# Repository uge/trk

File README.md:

# nrf9151 based picoballoon tracker in kicad

This repo contains a KiCad 8.0 project which hopes to implement a low power tracker for pico-balloons
based on the nRF9151 module and a WSPR protocol modulator.

## Why the nRF9151?

The nRF9151 is marketed with emphasis on cellular data and GPS capabilities with optimization for power.
Trackers are one category of intended applications and the device and software stack have provisions for 
aggressive power saving modes. Even if the cellular data connectivity feature is not used, the nrf9151
is a power efficient microcontroller with an embedded GPS.

The cellular functionality opens up the possibility of eventually using NTN services such as Skylo or Starlink.

## WSPR modulator

The Si5351 is a common frequency synthesizer used to implement the WSPR protocol. This design opts
for the TI CDCE6214 in hopes of reducing power consumption and to try something different.

## Power conversion

Following the Traquito's example, this design uses buck-boost converters to adapt to varying and lower voltages.
This design uses the TI TPS631010 which can operate at input voltages from 1.6V to 5.5V. There are two
buck-boost converters for the 1.8V and 3.3V supplies respectively.

## Manufacturing

This design is targeted at JLCPCB 4 layer design rules and includes JLCPCB part numbers in the BOM.

## License and Copyright

Copyright 2024 - Eugene Feinberg (ugeook at gmail dot com)

Licensed under Creative Commons Attribution-NonCommercial 4.0 International Public License

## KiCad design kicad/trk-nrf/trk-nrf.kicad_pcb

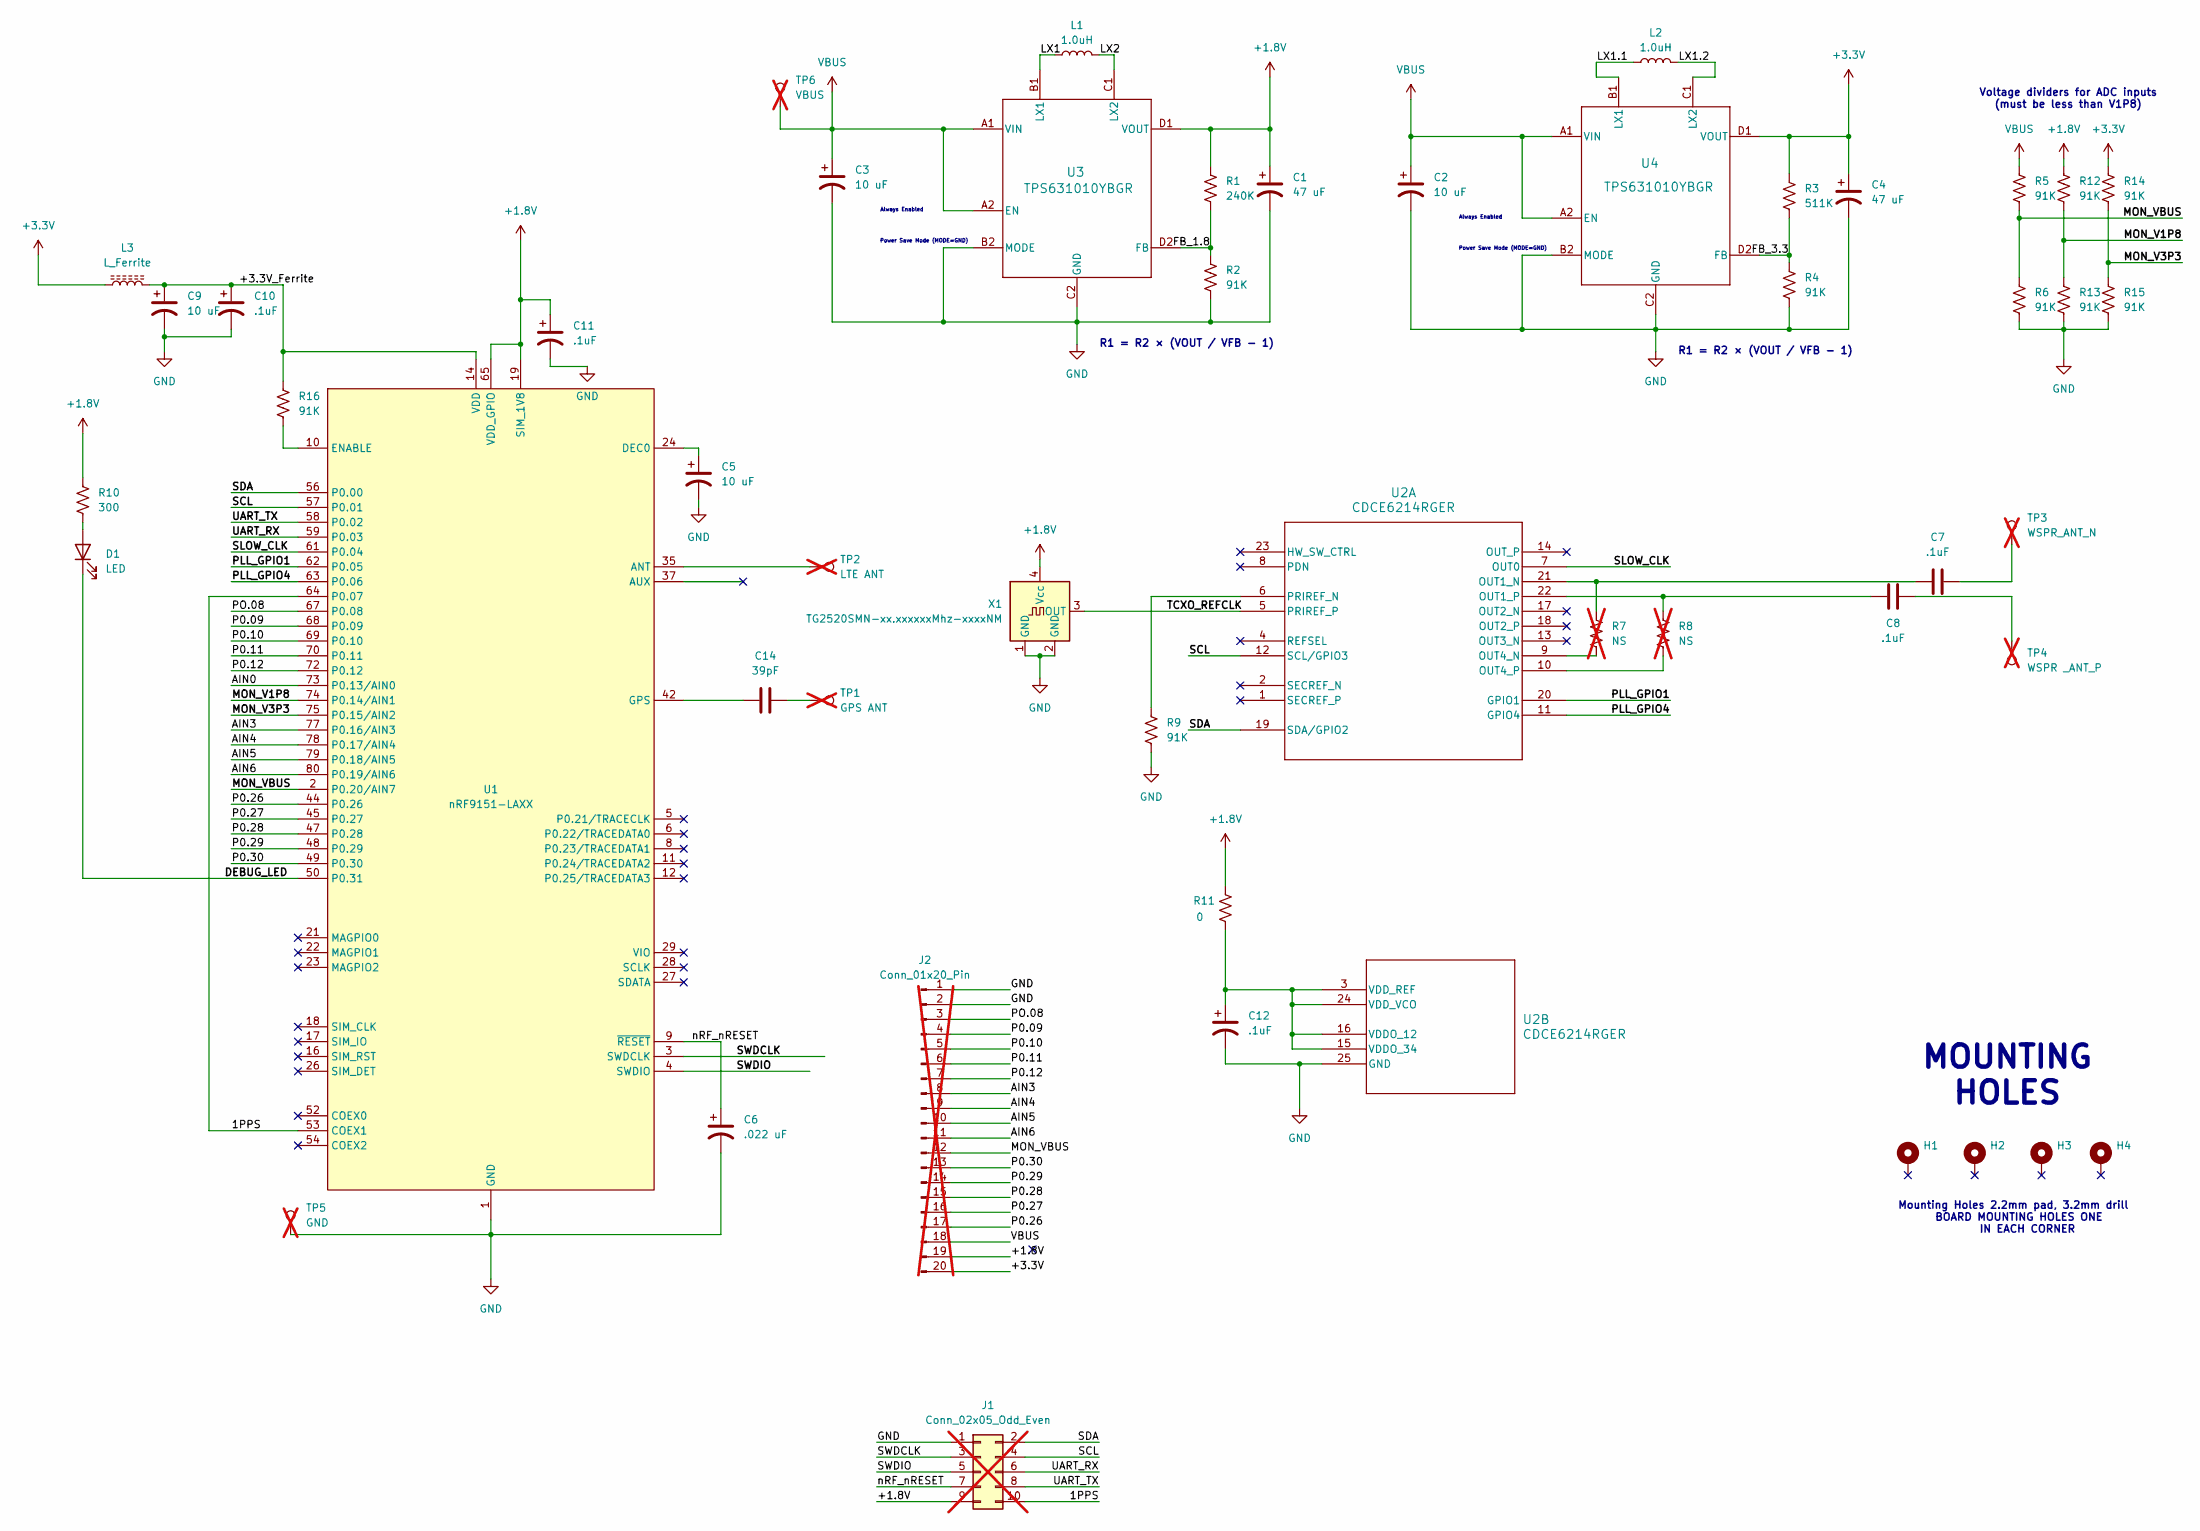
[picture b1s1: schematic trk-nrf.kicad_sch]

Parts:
C1, C4: 47 uF; C_0805_2012Metric; JLCPCB Part Number C16780
C2, C3, C5, C9: 10 uF; C_0603_1608Metric; JLCPCB Part Number C1691
C6: .022 uF; C_0402_1005Metric; JLCPCB Part Number C60474
C7, C8, C10, C11, C12: .1uF; C_0402_1005Metric; JLCPCB Part Number C1525
C14: 39pF; C_0402_1005Metric; JLCPCB Part Number C342946
D1: LED; LED_0402_1005Metric; JLCPCB Part Number C3007519
H1, H2, H3, H4: MountingHole_Pad_MP; MountingHole_2.2mm_M2_ISO7380_Pad
J1: Conn_02x05_Odd_Even; PinHeader_2x05_P1.00mm_Vertical_SMD; not fitted
J2: Conn_01x20_Pin; Hirose_FH12-20S-0.5SH_1x20-1MP_P0.50mm_Horizontal; not fitted
L1, L2: 1.0uH; L_Murata_DFE201610P; JLCPCB Part Number C92921
L3: L_Ferrite; L_0805_2012Metric; JLCPCB Part Number C12389
R1: 240K; R_0402_1005Metric; JLCPCB Part Number C64043
R2, R4, R5, R6, R9, R12, R13, R14, R15, R16: 91K; R_0402_1005Metric; JLCPCB Part Number C25573
R3: 511K; R_0402_1005Metric; JLCPCB Part Number C64042
R7, R8: NS; R_0402_1005Metric; not fitted
R10: 300; R_0402_1005Metric; JLCPCB Part Number C25159
R11: 0; R_0402_1005Metric; JLCPCB Part Number C17168
TP1: GPS ANT; TestPoint_Pad_1.5x1.5mm; not fitted
TP2: LTE ANT; TestPoint_Pad_1.5x1.5mm; not fitted
TP3: WSPR_ANT_N; TestPoint_THTPad_D1.5mm_Drill0.7mm; not fitted
TP4: WSPR _ANT_P; TestPoint_THTPad_D1.5mm_Drill0.7mm; not fitted
TP5: GND; TestPoint_THTPad_D1.5mm_Drill0.7mm; not fitted
TP6: VBUS; TestPoint_THTPad_D1.5mm_Drill0.7mm; not fitted
U1: nRF9151-LAXX; LGA_9151_12.1x11.1mm; JLCPCB Part Number C22397843
U2: CDCE6214RGER; VQFN24_RGE_TEX; JLCPCB Part Number C3608351
U3, U4: TPS631010YBGR; YBG0008; JLCPCB Part Number C6719123
X1: TG2520SMN-xx.xxxxxxMhz-xxxxNM; Oscillator_SMD_SeikoEpson_TG2520SMN-xxx-xxxxxx-4Pin_2.5x2.0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; JLCPCB Part Number C5590921

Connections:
+1.8V: C1.1, C11.1, J1.9, J2.19, R1.1, R10.1, R11.1, R12.1, U1.19 (SIM_1V8), U1.65 (VDD_GPIO), U3.D1 (VOUT), X1.4 (Vcc)
+3.3V: C4.1, J2.20, L3.1, R3.1, R14.1, U4.D1 (VOUT)
/1PPS: J1.10, U1.53 (COEX1), U1.64 (P0.07)
/+3.3V_Ferrite: C9.1, C10.1, L3.2, R16.1, U1.14 (VDD)
/AIN0: U1.73 (P0.13/AIN0)
/AIN3: J2.8, U1.77 (P0.16/AIN3)
/AIN4: J2.9, U1.78 (P0.17/AIN4)
/AIN5: J2.10, U1.79 (P0.18/AIN5)
/AIN6: J2.11, U1.80 (P0.19/AIN6)
/DEBUG_LED: D1.1 (K), U1.50 (P0.31)
/FB_1.8: R1.2, R2.1, U3.D2 (FB)
/FB_3.3: R3.2, R4.1, U4.D2 (FB)
/LX1: L1.1, U3.B1 (LX1)
/LX1.1: L2.1, U4.B1 (LX1)
/LX1.2: L2.2, U4.C1 (LX2)
/LX2: L1.2, U3.C1 (LX2)
/MON_V1P8: R12.2, R13.1, U1.74 (P0.14/AIN1)
/MON_V3P3: R14.2, R15.1, U1.75 (P0.15/AIN2)
/MON_VBUS: J2.12, R5.2, R6.1, U1.2 (P0.20/AIN7)
/P0.09: J2.4, U1.68 (P0.09)
/P0.10: J2.5, U1.69 (P0.10)
/P0.11: J2.6, U1.70 (P0.11)
/P0.12: J2.7, U1.72 (P0.12)
/P0.26: J2.17, U1.44 (P0.26)
/P0.27: J2.16, U1.45 (P0.27)
/P0.28: J2.15, U1.47 (P0.28)
/P0.29: J2.14, U1.48 (P0.29)
/P0.30: J2.13, U1.49 (P0.30)
/PLL_GPIO1: U1.62 (P0.05), U2.20 (GPIO1)
/PLL_GPIO4: U1.63 (P0.06), U2.11 (GPIO4)
/PO.08: J2.3, U1.67 (P0.08)
/SCL: J1.4, U1.57 (P0.01), U2.12 (SCL/GPIO3)
/SDA: J1.2, U1.56 (P0.00), U2.19 (SDA/GPIO2)
/SLOW_CLK: U1.61 (P0.04), U2.7 (OUT0)
/SWDCLK: J1.3, U1.3 (SWDCLK)
/SWDIO: J1.5, U1.4 (SWDIO)
/TCXO_REFCLK: U2.5 (PRIREF_P), X1.3 (OUT)
/UART_RX: J1.6, U1.59 (P0.03)
/UART_TX: J1.8, U1.58 (P0.02)
/nRF_nRESET: C6.1, J1.7, U1.9 (~RESET)
GND: C1.2, C2.2, C3.2, C4.2, C5.2, C6.2, C9.2, C10.2, C11.2, C12.2, J1.1, J2.1, J2.2, R2.2, R4.2, R6.2, R9.2, R13.2, R15.2, TP5.1, U1.1 (GND), U1.7 (GND), U1.13 (GND), U1.15 (GND), U1.20 (GND), U1.25 (GND), U1.30 (GND), U1.34 (GND), U1.36 (GND), U1.38 (GND), U1.39 (GND), U1.40 (GND), U1.41 (GND), U1.43 (GND), U1.46 (GND), U1.51 (GND), U1.55 (GND), U1.60 (GND), U1.66 (GND), U1.71 (GND), U1.76 (GND), U1.105 (GND), U1.106 (GND), U1.107 (GND), U1.108 (GND), U1.109 (GND), U1.110 (GND), U1.111 (GND), U1.112 (GND), U1.113 (GND), U2.25 (GND), U3.B2 (MODE), U3.C2 (GND), U4.B2 (MODE), U4.C2 (GND), X1.1 (GND), X1.2 (GND)
unnamed: C7.2, TP3.1
unnamed: C8.2, TP4.1
unnamed: C14.2, TP1.1
unnamed: D1.2 (A), R10.2
unnamed: TP2.1, U1.35 (ANT)
unnamed: C5.1, U1.24 (DEC0)
unnamed: R16.2, U1.10 (ENABLE)
unnamed: C14.1, U1.42 (GPS)
unnamed: C7.1, R7.1, U2.21 (OUT1_N)
unnamed: C8.1, R8.1, U2.22 (OUT1_P)
unnamed: R7.2, U2.9 (OUT4_N)
unnamed: R8.2, U2.10 (OUT4_P)
unnamed: R9.1, U2.6 (PRIREF_N)
unnamed: C12.1, R11.2, U2.3 (VDD_REF), U2.15 (VDDO_34), U2.16 (VDDO_12), U2.24 (VDD_VCO)
VBUS: C2.1, C3.1, J2.18, R5.1, TP6.1, U3.A1 (VIN), U3.A2 (EN), U4.A1 (VIN), U4.A2 (EN)

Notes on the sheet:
Mounting Holes 2.2mm pad, 3.2mm drill BOARD MOUNTING HOLES ONE IN EACH CORNER
MOUNTING HOLES
Power Save Mode (MODE=GND)
Always Enabled
R1 = R2 × (VOUT / VFB - 1)
Voltage dividers for ADC inputs (must be less than V1P8)

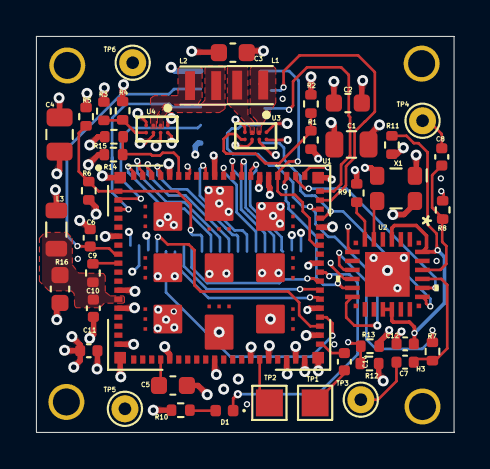
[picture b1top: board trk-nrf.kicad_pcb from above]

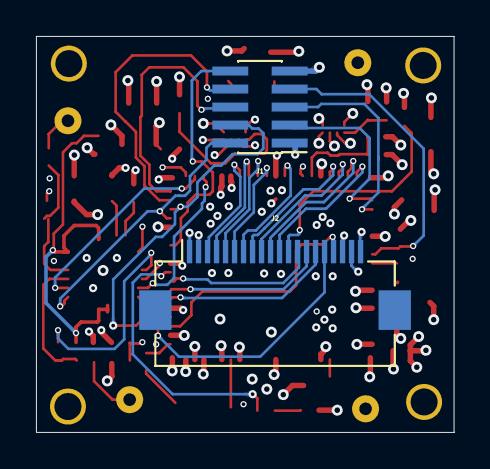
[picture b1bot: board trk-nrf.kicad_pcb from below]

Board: 4 copper layers, 23.2 x 22.0 mm, 50 parts (2 on the bottom side), 55 nets.

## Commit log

2024-11-29 Updates - pre-routing
2024-12-02 Schematic edits and drc changes
2024-12-02 Updated schematic
2024-12-04 Add second ground and freeroute board
2024-12-09 Board detailed routing by Estifanos Nega
2024-12-10 - Add license and update README.md
